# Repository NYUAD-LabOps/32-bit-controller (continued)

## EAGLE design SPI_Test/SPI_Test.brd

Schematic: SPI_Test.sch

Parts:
C1, C2, C3, C4, C5, C7, C8, C9, C14, C15, C19, C20, C23, C28, C29, C31, C43, C44, C45, C47, C48, C49, C50, C51, C52, C53, C54, C61, C62, C63, C64, C65, C66, C67, C68, C69, C91, C92, C93, C94, C95, C96, C97, C98, C99, C121, C122, C123, C124, C125, C126, C127, C128, C129, C151, C152, C153, C154, C155, C156, C157, C158, C159, C181, C182, C183, C184, C185, C186, C187, C188, C189: 0.1uF; 0402
C6, C46, C55, C70, C100, C130, C160, C190: 1uF; 0402
C10, C11, C39, C40, C57, C58, C87, C88, C117, C118, C147, C148, C177, C178: 12pF; 0402
C12, C13: 18pF; 0402
C21, C26, C56, C71, C101, C131, C161, C191: 10uF; 0402
C41, C42, C59, C60, C89, C90, C119, C120, C149, C150, C179, C180: 10pF; 0402
J1, J4, J6, J10, J15, J19, J23: 10-pos; 2X5
J3, J5, J9, J14, J18, J22: CONN_05X2PTH; 2X5
J13: 4-pos; 1X4_3.81MM_PITCH
L2: 2.2uH; 1008
LED2: Green; 0805
R1, R2, R3, R5, R6, R8, R10, R13, R15: 10K0; 0402
R4: 2K2; 0402
R12: 470R0; 0402
U1, U3, U6, U8, U10, U12: RENESAS_R7FS5D37A3A01CFM#AA0PLQP0064KB-C_REN-M; PLQP0064KB-C_REN-M
U2: S7G2LQFP176; LQFP176_24X24
X2, X3, X5, X7, X9, X11, X13: 32.768KHz; SMD_X_2_PADS
X4: 24MHz; SMD_3225
Y1, Y3, Y5, Y7, Y9, Y11: XTAL_12MHZ_ABM8G-12.000MHZ-B4Y-T; CRYSTAL_ABM8G_ABR

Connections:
DFI_01_A1: U1.50 (50/P501), U3.50 (50/P501), U6.50 (50/P501), U8.50 (50/P501), U10.50 (50/P501), U12.50 (50/P501)
DFI_02_A1: U1.62 (62/P002), U3.62 (62/P002), U6.62 (62/P002), U8.62 (62/P002), U10.62 (62/P002), U12.62 (62/P002)
DFO_01_A1: U1.30 (30/P302), U3.30 (30/P302), U6.30 (30/P302), U8.30 (30/P302), U10.30 (30/P302), U12.30 (30/P302)
DFO_02_A1: U1.41 (41/P107), U3.41 (41/P107), U6.41 (41/P107), U8.41 (41/P107), U10.41 (41/P107), U12.41 (41/P107)
DFO_03_A1: U1.42 (42/P106), U3.42 (42/P106), U6.42 (42/P106), U8.42 (42/P106), U10.42 (42/P106), U12.42 (42/P106)
DIR_M0A1: U1.15 (15/P408), U3.15 (15/P408), U6.15 (15/P408), U8.15 (15/P408), U10.15 (15/P408), U12.15 (15/P408)
DIR_M1A1: U1.3 (3/P402), U3.3 (3/P402), U6.3 (3/P402), U8.3 (3/P402), U10.3 (3/P402), U12.3 (3/P402)
ENABLE_M0A1: U1.14 (14/P409), U3.14 (14/P409), U6.14 (14/P409), U8.14 (14/P409), U10.14 (14/P409), U12.14 (14/P409)
ENABLE_M1A1: U1.2 (2/P401), U3.2 (2/P401), U6.2 (2/P401), U8.2 (2/P401), U10.2 (2/P401), U12.2 (2/P401)
ESTOP: U2.69 (P2_0(INPUT_ONLY))
ESTOP_A1: U1.27 (27/P200), U3.27 (27/P200), U6.27 (27/P200), U8.27 (27/P200), U10.27 (27/P200), U12.27 (27/P200)
GND: C1.P$1 (1), C2.P$1 (1), C3.P$1 (1), C4.P$1 (1), C5.P$2 (2), C6.P$2 (2), C7.P$1 (1), C8.P$1 (1), C9.P$2 (2), C10.P$2 (2), C11.P$2 (2), C12.P$2 (2), C13.P$2 (2), C14.P$1 (1), C15.P$1 (1), C19.P$2 (2), C20.P$2 (2), C21.P$2 (2), C23.P$1 (1), C26.P$2 (2), C28.P$2 (2), C29.P$2 (2), C31.P$2 (2), C39.P$2 (2), C40.P$2 (2), C41.P$2 (2), C42.P$2 (2), C43.P$2 (2), C44.P$1 (1), C45.P$1 (1), C46.P$1 (1), C47.P$2 (2), C48.P$2 (2), C49.P$2 (2), C50.P$1 (1), C51.P$1 (1), C52.P$2 (2), C53.P$2 (2), C54.P$2 (2), C55.P$2 (2), C56.P$2 (2), C57.P$2 (2), C58.P$2 (2), C59.P$2 (2), C60.P$2 (2), C61.P$2 (2), C62.P$2 (2), C63.P$2 (2), C64.P$2 (2), C65.P$1 (1), C66.P$1 (1), C67.P$2 (2), C68.P$2 (2), C69.P$2 (2), C70.P$2 (2), C71.P$2 (2), C87.P$2 (2), C88.P$2 (2), C89.P$2 (2), C90.P$2 (2), C91.P$2 (2), C92.P$2 (2), C93.P$2 (2), C94.P$2 (2), C95.P$1 (1), C96.P$1 (1), C97.P$2 (2), C98.P$2 (2), C99.P$2 (2), C100.P$2 (2), C101.P$2 (2), C117.P$2 (2), C118.P$2 (2), C119.P$2 (2), C120.P$2 (2), C121.P$2 (2), C122.P$2 (2), C123.P$2 (2), C124.P$2 (2), C125.P$1 (1), C126.P$1 (1), C127.P$2 (2), C128.P$2 (2), C129.P$2 (2), C130.P$2 (2), C131.P$2 (2), C147.P$2 (2), C148.P$2 (2), C149.P$2 (2), C150.P$2 (2), C151.P$2 (2), C152.P$2 (2), C153.P$2 (2), C154.P$2 (2), C155.P$1 (1), C156.P$1 (1), C157.P$2 (2), C158.P$2 (2), C159.P$2 (2), C160.P$2 (2), C161.P$2 (2), C177.P$2 (2), C178.P$2 (2), C179.P$2 (2), C180.P$2 (2), C181.P$2 (2), C182.P$2 (2), C183.P$2 (2), C184.P$2 (2), C185.P$1 (1), C186.P$1 (1), C187.P$2 (2), C188.P$2 (2), C189.P$2 (2), C190.P$2 (2), C191.P$2 (2), J1.6, J1.8, J1.10, J3.1, J3.2, J4.6, J4.8, J4.10, J5.1, J5.2, J6.6, J6.8, J6.10, J9.1, J9.2, J10.6, J10.8, J10.10, J13.P$1, J13.P$3, J13.P$4, J14.1, J14.2, J15.6, J15.8, J15.10, J18.1, J18.2, J19.6, J19.8, J19.10, J22.1, J22.2, J23.6, J23.8, J23.10, LED2.2 (C), R1.P$1 (1), R2.P$1 (1), R4.P$1 (1), U1.8 (8/VSS), U1.17 (17/VSS_USB), U1.28 (28/VSS), U1.39 (39/VSS), U1.55 (55/VREFL), U1.58 (58/AVSS0), U1.59 (59/VREFL0), U2.22 (VSS1), U2.28 (AVSS_USBHS), U2.29 (PVSS_USBHS), U2.30 (VSS2_USBHS), U2.33 (VSS1_USBHS), U2.35 (VSSIO), U2.45 (VSS_USB), U2.60 (VSS(IO)2), U2.63 (VSS(IO/DCDC)), U2.66 (VCC_DCDC(IO/DCDC)), U2.83 (VSS(IO)3), U2.98 (VSS(IO)4), U2.111 (VSS(IO)5), U2.124 (VSS(IO)6), U2.139 (VSS(IO)7), U2.150 (VSS(IO)8), U2.153 (VREFL), U2.156 (AVSS0), U2.157 (VREFL0), U2.170 (VSS(IO)9), U3.8 (8/VSS), U3.17 (17/VSS_USB), U3.28 (28/VSS), U3.39 (39/VSS), U3.55 (55/VREFL), U3.58 (58/AVSS0), U3.59 (59/VREFL0), U6.8 (8/VSS), U6.17 (17/VSS_USB), U6.28 (28/VSS), U6.39 (39/VSS), U6.55 (55/VREFL), U6.58 (58/AVSS0), U6.59 (59/VREFL0), U8.8 (8/VSS), U8.17 (17/VSS_USB), U8.28 (28/VSS), U8.39 (39/VSS), U8.55 (55/VREFL), U8.58 (58/AVSS0), U8.59 (59/VREFL0), U10.8 (8/VSS), U10.17 (17/VSS_USB), U10.28 (28/VSS), U10.39 (39/VSS), U10.55 (55/VREFL), U10.58 (58/AVSS0), U10.59 (59/VREFL0), U12.8 (8/VSS), U12.17 (17/VSS_USB), U12.28 (28/VSS), U12.39 (39/VSS), U12.55 (55/VREFL), U12.58 (58/AVSS0), U12.59 (59/VREFL0), X4.2, X4.4, Y1.2, Y1.4, Y3.2, Y3.4, Y5.2, Y5.4, Y7.2, Y7.4, Y9.2, Y9.4, Y11.2, Y11.4
HLFB_M0A1: U1.13 (13/P410), U3.13 (13/P410), U6.13 (13/P410), U8.13 (13/P410), U10.13 (13/P410), U12.13 (13/P410)
HLFB_M1A1: U1.1 (1/P400), U3.1 (1/P400), U6.1 (1/P400), U8.1 (1/P400), U10.1 (1/P400), U12.1 (1/P400)
LS_01_A1: U1.23 (23/P205), U3.23 (23/P205), U6.23 (23/P205), U8.23 (23/P205), U10.23 (23/P205), U12.23 (23/P205)
LS_02_A1: U1.53 (53/P015), U3.53 (53/P015), U6.53 (53/P015), U8.53 (53/P015), U10.53 (53/P015), U12.53 (53/P015)
LS_03_A1: U1.64 (64/P000), U3.64 (64/P000), U6.64 (64/P000), U8.64 (64/P000), U10.64 (64/P000), U12.64 (64/P000)
LS_04_A1: U1.63 (63/P001), U3.63 (63/P001), U6.63 (63/P001), U8.63 (63/P001), U10.63 (63/P001), U12.63 (63/P001)
LS_05: U2.81 (P3_5)
LS_06: U2.82 (P3_4)
MISO: J3.9, J3.10, J5.9, J5.10, J9.9, J9.10, J14.9, J14.10, J18.9, J18.10, J22.9, J22.10, U1.48 (48/P100), U2.132 (P1_0), U3.48 (48/P100), U6.48 (48/P100), U8.48 (48/P100), U10.48 (48/P100), U12.48 (48/P100)
MOSI: J3.7, J3.8, J5.7, J5.8, J9.7, J9.8, J14.7, J14.8, J18.7, J18.8, J22.7, J22.8, U1.47 (47/P101), U2.131 (P1_1), U3.47 (47/P101), U6.47 (47/P101), U8.47 (47/P101), U10.47 (47/P101), U12.47 (47/P101)
unnamed: C8.P$2 (2), U2.148 (VCL2)
unnamed: C9.P$1 (1), U2.19 (VCLO)
unnamed: LED2.1 (A), R12.P$1 (1)
unnamed: C5.P$1 (1), U2.62 (VCL1)
unnamed: R2.P$2 (2), U2.64 (VLO1(DCDC))
unnamed: R1.P$2 (2), U2.65 (VLO2(DCDC))
unnamed: R4.P$2 (2), U2.27 (USBHS_RREF)
unnamed: U1.18 (18/USB_DM), U3.18 (18/USB_DM), U6.18 (18/USB_DM), U8.18 (18/USB_DM), U10.18 (18/USB_DM), U12.18 (18/USB_DM)
unnamed: U1.19 (19/USB_DP), U3.19 (19/USB_DP), U6.19 (19/USB_DP), U8.19 (19/USB_DP), U10.19 (19/USB_DP), U12.19 (19/USB_DP)
unnamed: U1.26 (26/P201/MD), U3.26 (26/P201/MD), U6.26 (26/P201/MD), U8.26 (26/P201/MD), U10.26 (26/P201/MD), U12.26 (26/P201/MD)
unnamed: U1.36 (36/P111), U3.36 (36/P111), U6.36 (36/P111), U8.36 (36/P111), U10.36 (36/P111), U12.36 (36/P111)
unnamed: U1.37 (37/P112), U3.37 (37/P112), U6.37 (37/P112), U8.37 (37/P112), U10.37 (37/P112), U12.37 (37/P112)
unnamed: U1.40 (40/VCL), U3.40 (40/VCL), U6.40 (40/VCL), U8.40 (40/VCL), U10.40 (40/VCL), U12.40 (40/VCL)
unnamed: U1.43 (43/P105), U3.43 (43/P105), U6.43 (43/P105), U8.43 (43/P105), U10.43 (43/P105), U12.43 (43/P105)
unnamed: U1.44 (44/P104), U3.44 (44/P104), U6.44 (44/P104), U8.44 (44/P104), U10.44 (44/P104), U12.44 (44/P104)
P0_00: U2.169 (P0_0/AN0\00)
P0_01: U2.168 (P0_1/AN001)
P0_02: U2.167 (P0_2/AN002)
P0_03: U2.166 (P0_3/PGAVSS000)
P0_04: U2.165 (P0_4/AN100)
P0_05: U2.164 (P0_5/AN101)
P0_06: U2.163 (P0_6/AN102)
P0_07: U2.162 (P0_7/PGVSS100)
P0_08: U2.161 (P0_8/AN003)
P0_09: U2.160 (P0_9/AN004)
P0_10: U2.159 (P0_10/AN103)
P0_14: U2.152 (P0_14/DA0/AN005/AN105)
P0_15: U2.151 (P0_15/DA1/AN006/AN106)
P1_11: U2.92 (P1_11)
P1_12: U2.93 (P1_12)
P1_13: U2.94 (P1_13)
P1_14: U2.95 (P1_14)
P1_15: U2.96 (P1_15)
P2_01: U2.68 (P2_1/MD)
P2_02: U2.54 (P2_2)
P2_03: U2.53 (P2_3)
P2_04: U2.52 (P2_4)
P2_05: U2.51 (P2_5)
P2_06: U2.50 (P2_6)
P2_07: U2.49 (P2_7)
P3_01: U2.87 (P3_1)
P3_02: U2.86 (P3_2)
P3_03: U2.85 (P3_3)
P3_06: U2.80 (P3_6)
P3_07: U2.79 (P3_7)
P3_08: U2.78 (P3_8)
P3_09: U2.77 (P3_9)
P3_10: U2.76 (P3_10)
P3_11: U2.75 (P3_11)
P3_12: U2.74 (P3_12)
P3_13: U2.55 (P3_13)
P3_14: U2.56 (P3_14)
P3_15: U2.57 (P3_15)
P4_00: U2.1 (P4_0)
P4_01: U2.2 (P4_1)
P4_02: U2.3 (P4_2)
P4_03: U2.4 (P4_3)
P4_04: U2.5 (P4_4)
P4_05: U2.6 (P4_5)
P4_06: U2.7 (P4_6)
P4_08: U2.43 (P4_8)
P4_09: U2.42 (P4_9)
P4_10: U2.41 (P4_10)
P4_11: U2.40 (P4_11)
P4_12: U2.39 (P4_12)
P4_13: U2.38 (P4_13)
P4_14: U2.37 (P4_14)
P4_15: U2.36 (P4_15)
P5_00: U2.140 (P5_0/AN016)
P5_01: U2.141 (P5_1/AN116)
P5_02: U2.142 (P5_2/AN017)
P5_03: U2.143 (P5_3/AN117)
P5_04: U2.144 (P5_4/AN018)
P5_05: U2.145 (P5_5/AN118)
P5_06: U2.146 (P5_6/AN019)
P5_07: U2.147 (P5_7/AN119)
P5_11: U2.176 (P5_11)
P5_12: U2.175 (P5_12)
P5_13: U2.174 (P5_13)
P6_01: U2.121 (P6_1)
P6_02: U2.120 (P6_2)
P6_03: U2.119 (P6_3)
P6_04: U2.118 (P6_4)
P6_05: U2.117 (P6_5)
P6_06: U2.116 (P6_6)
P6_07: U2.115 (P6_7)
P6_08: U2.99 (P6_8)
P6_09: U2.100 (P6_9)
P6_10: U2.101 (P6_10)
P6_11: U2.102 (P6_11)
P6_12: U2.103 (P6_12)
P6_13: U2.104 (P6_13)
P6_14: U2.105 (P6_14)
P6_15: U2.106 (P6_15)
P7_00: U2.8 (P7_0)
P7_01: U2.9 (P7_1)
P7_02: U2.10 (P7_2)
P7_03: U2.11 (P7_3)
P7_04: U2.12 (P7_4)
P7_05: U2.13 (P7_5)
P7_06: U2.14 (P7_6)
P7_07: U2.15 (P7_7)
P8_00: U2.133 (P8_0)
P8_01: U2.134 (P8_1)
P8_02: U2.135 (P8_2)
P8_03: U2.136 (P8_3)
P8_04: U2.137 (P8_4)
P8_05: U2.173 (P8_5)
P8_06: U2.172 (P8_6)
P9_00: U2.58 (P9_0)
P9_01: U2.59 (P9_1)
P9_05: U2.73 (P9_5)
P9_06: U2.72 (P9_6)
P9_07: U2.71 (P9_7)
P9_08: U2.70 (P9_8)
PA_00: U2.114 (PA_0)
PA_01: U2.113 (PA_1)
PA_08: U2.107 (PA_8)
PA_09: U2.108 (PA_9)
PA_10: U2.109 (PA_10)
PB_00: U2.16 (PB_0)
RELAY_1_A1: U1.24 (24/P204), U3.24 (24/P204), U6.24 (24/P204), U8.24 (24/P204), U10.24 (24/P204), U12.24 (24/P204)
RELAY_2_A1: U1.21 (21/P207), U3.21 (21/P207), U6.21 (21/P207), U8.21 (21/P207), U10.21 (21/P207), U12.21 (21/P207)
RELAY_3_A1: U1.22 (22/P206), U3.22 (22/P206), U6.22 (22/P206), U8.22 (22/P206), U10.22 (22/P206), U12.22 (22/P206)
RELAY_4_A1: U1.31 (31/P301), U3.31 (31/P301), U6.31 (31/P301), U8.31 (31/P301), U10.31 (31/P301), U12.31 (31/P301)
RESET: C26.P$1 (1), J1.9, R3.P$1 (1), U2.67 (RES#)
RESET_A1: C56.P$1 (1), C71.P$1 (1), C101.P$1 (1), C131.P$1 (1), C161.P$1 (1), C191.P$1 (1), J4.9, J6.9, J10.9, J15.9, J19.9, J23.9, R5.P$1 (1), R6.P$1 (1), R8.P$1 (1), R10.P$1 (1), R13.P$1 (1), R15.P$1 (1), U1.25 (25/RES), U3.25 (25/RES), U6.25 (25/RES), U8.25 (25/RES), U10.25 (25/RES), U12.25 (25/RES)
SCLK: J3.5, J3.6, J5.5, J5.6, J9.5, J9.6, J14.5, J14.6, J18.5, J18.6, J22.5, J22.6, U1.46 (46/P102), U2.130 (P1_2), U3.46 (46/P102), U6.46 (46/P102), U8.46 (46/P102), U10.46 (46/P102), U12.46 (46/P102)
SSL0_A1_01: J3.3, J3.4, U1.45 (45/P103), U2.129 (P1_3)
SSL0_A1_02: J5.3, J5.4, U2.128 (P1_4), U3.45 (45/P103)
SSL0_A1_03: J9.3, J9.4, U2.127 (P1_5), U6.45 (45/P103)
SSL0_A1_04: J14.3, J14.4, U2.126 (P1_6), U8.45 (45/P103)
SSL0_A1_05: J18.3, J18.4, U2.125 (P1_7), U10.45 (45/P103)
SSL0_A1_06: J22.3, J22.4, U2.122 (P6_0), U12.45 (45/P103)
STEP_M0A1: U1.16 (16/P407), U3.16 (16/P407), U6.16 (16/P407), U8.16 (16/P407), U10.16 (16/P407), U12.16 (16/P407)
STEP_M1A1: U1.12 (12/P411), U3.12 (12/P411), U6.12 (12/P411), U8.12 (12/P411), U10.12 (12/P411), U12.12 (12/P411)
TCK: J1.7, J4.7, J6.7, J10.7, J15.7, J19.7, J23.7, U1.32 (32/P300/TCK/SWCLK), U2.88 (P3_0), U3.32 (32/P300/TCK/SWCLK), U6.32 (32/P300/TCK/SWCLK), U8.32 (32/P300/TCK/SWCLK), U10.32 (32/P300/TCK/SWCLK), U12.32 (32/P300/TCK/SWCLK)
TDI: J1.1, J4.1, J6.1, J10.1, J15.1, J19.1, J23.1, U1.35 (35/P110/TDI), U2.91 (P1_10), U3.35 (35/P110/TDI), U6.35 (35/P110/TDI), U8.35 (35/P110/TDI), U10.35 (35/P110/TDI), U12.35 (35/P110/TDI)
TDO: J1.3, J4.3, J6.3, J10.3, J15.3, J19.3, J23.3, U1.34 (34/P109/TDO/SWO), U2.90 (P1_9), U3.34 (34/P109/TDO/SWO), U6.34 (34/P109/TDO/SWO), U8.34 (34/P109/TDO/SWO), U10.34 (34/P109/TDO/SWO), U12.34 (34/P109/TDO/SWO)
TMS: J1.5, J4.5, J6.5, J10.5, J15.5, J19.5, J23.5, U1.33 (33/P108/TMS/SWDIO), U2.89 (P1_8), U3.33 (33/P108/TMS/SWDIO), U6.33 (33/P108/TMS/SWDIO), U8.33 (33/P108/TMS/SWDIO), U10.33 (33/P108/TMS/SWDIO), U12.33 (33/P108/TMS/SWDIO)
USBHS_DN: U2.31 (USBHS_DM)
USBHS_DP: U2.32 (USBHS_DP)
USBHS_VBUS: U2.17 (PB_1)
USB_DN: U2.46 (USB_DM)
USB_DP: U2.47 (USB_DP)
USB_VBUS_B: U2.44 (P4_7)
VBATT_M1A1: U1.4 (4/VBATT), U3.4 (4/VBATT), U6.4 (4/VBATT), U8.4 (4/VBATT), U10.4 (4/VBATT), U12.4 (4/VBATT)
VCL0_A1: C50.P$2 (2), C65.P$2 (2), C95.P$2 (2), C125.P$2 (2), C155.P$2 (2), C185.P$2 (2), U1.5 (5/VCL0), U3.5 (5/VCL0), U6.5 (5/VCL0), U8.5 (5/VCL0), U10.5 (5/VCL0), U12.5 (5/VCL0)
VCL_F(FLASH): C7.P$2 (2), U2.112 (VCL_F(FLASH))
VDD: C1.P$2 (2), C2.P$2 (2), C3.P$2 (2), C4.P$2 (2), C6.P$1 (1), C14.P$2 (2), C15.P$2 (2), C19.P$1 (1), C20.P$1 (1), C21.P$1 (1), C23.P$2 (2), C28.P$1 (1), C29.P$1 (1), C31.P$1 (1), C43.P$1 (1), C44.P$2 (2), C45.P$2 (2), C46.P$2 (2), C47.P$1 (1), C48.P$1 (1), C49.P$1 (1), C51.P$2 (2), C52.P$1 (1), C53.P$1 (1), C54.P$1 (1), C55.P$1 (1), C61.P$1 (1), C62.P$1 (1), C63.P$1 (1), C64.P$1 (1), C66.P$2 (2), C67.P$1 (1), C68.P$1 (1), C69.P$1 (1), C70.P$1 (1), C91.P$1 (1), C92.P$1 (1), C93.P$1 (1), C94.P$1 (1), C96.P$2 (2), C97.P$1 (1), C98.P$1 (1), C99.P$1 (1), C100.P$1 (1), C121.P$1 (1), C122.P$1 (1), C123.P$1 (1), C124.P$1 (1), C126.P$2 (2), C127.P$1 (1), C128.P$1 (1), C129.P$1 (1), C130.P$1 (1), C151.P$1 (1), C152.P$1 (1), C153.P$1 (1), C154.P$1 (1), C156.P$2 (2), C157.P$1 (1), C158.P$1 (1), C159.P$1 (1), C160.P$1 (1), C181.P$1 (1), C182.P$1 (1), C183.P$1 (1), C184.P$1 (1), C186.P$2 (2), C187.P$1 (1), C188.P$1 (1), C189.P$1 (1), C190.P$1 (1), J1.2, J1.4, J4.2, J4.4, J6.2, J6.4, J10.2, J10.4, J15.2, J15.4, J19.2, J19.4, J23.2, J23.4, L2.2, R3.P$2 (2), R5.P$2 (2), R6.P$2 (2), R8.P$2 (2), R10.P$2 (2), R12.P$2 (2), R13.P$2 (2), R15.P$2 (2), U1.11 (11/VCC), U1.20 (20/VCC_USB), U1.29 (29/VCC), U1.38 (38/VCC), U1.51 (51/VCC), U1.56 (56/VREFH), U1.57 (57/AVCC0), U1.60 (60/VREFH0), U2.25 (VCC1), U2.26 (AVCC_SUBHS), U2.34 (VCC_USBHS), U2.48 (VCC_USB), U2.61 (VCC(IO)2), U2.84 (VCC(IO)3), U2.97 (VCC(IO)4), U2.110 (VCC(IO)5), U2.123 (VCC(IO)6), U2.138 (VCC(IO)7), U2.149 (VCC(IO)8), U2.154 (VREFH), U2.155 (AVCC0), U2.158 (VREFH0), U2.171 (VCC(IO)9), U3.11 (11/VCC), U3.20 (20/VCC_USB), U3.29 (29/VCC), U3.38 (38/VCC), U3.51 (51/VCC), U3.56 (56/VREFH), U3.57 (57/AVCC0), U3.60 (60/VREFH0), U6.11 (11/VCC), U6.20 (20/VCC_USB), U6.29 (29/VCC), U6.38 (38/VCC), U6.51 (51/VCC), U6.56 (56/VREFH), U6.57 (57/AVCC0), U6.60 (60/VREFH0), U8.11 (11/VCC), U8.20 (20/VCC_USB), U8.29 (29/VCC), U8.38 (38/VCC), U8.51 (51/VCC), U8.56 (56/VREFH), U8.57 (57/AVCC0), U8.60 (60/VREFH0), U10.11 (11/VCC), U10.20 (20/VCC_USB), U10.29 (29/VCC), U10.38 (38/VCC), U10.51 (51/VCC), U10.56 (56/VREFH), U10.57 (57/AVCC0), U10.60 (60/VREFH0), U12.11 (11/VCC), U12.20 (20/VCC_USB), U12.29 (29/VCC), U12.38 (38/VCC), U12.51 (51/VCC), U12.56 (56/VREFH), U12.57 (57/AVCC0), U12.60 (60/VREFH0)
VDDIN: J13.P$2, L2.1
XCIN: C10.P$1 (1), U2.20 (XCIN), X3.P$1
XCIN_A1: C39.P$1 (1), C57.P$1 (1), C87.P$1 (1), C117.P$1 (1), C147.P$1 (1), C177.P$1 (1), U1.6 (6/XCIN), U3.6 (6/XCIN), U6.6 (6/XCIN), U8.6 (6/XCIN), U10.6 (6/XCIN), U12.6 (6/XCIN), X2.P$1, X5.P$1, X7.P$1, X9.P$1, X11.P$1, X13.P$1
XCOUT: C11.P$1 (1), U2.21 (XCOUT), X3.P$2
XCOUT_A1: C40.P$1 (1), C58.P$1 (1), C88.P$1 (1), C118.P$1 (1), C148.P$1 (1), C178.P$1 (1), U1.7 (7/XCOUT), U3.7 (7/XCOUT), U6.7 (7/XCOUT), U8.7 (7/XCOUT), U10.7 (7/XCOUT), U12.7 (7/XCOUT), X2.P$2, X5.P$2, X7.P$2, X9.P$2, X11.P$2, X13.P$2
XTAL1: C12.P$1 (1), U2.23 (P2_13/XTAL), X4.1
XTAL1_A1: C41.P$1 (1), C59.P$1 (1), C89.P$1 (1), C119.P$1 (1), C149.P$1 (1), C179.P$1 (1), U1.9 (9/XTAL), U3.9 (9/XTAL), U6.9 (9/XTAL), U8.9 (9/XTAL), U10.9 (9/XTAL), U12.9 (9/XTAL), Y1.3, Y3.3, Y5.3, Y7.3, Y9.3, Y11.3
XTAL2: C13.P$1 (1), U2.24 (P2_12/EXTAL), X4.3
XTAL2_A1: C42.P$1 (1), C60.P$1 (1), C90.P$1 (1), C120.P$1 (1), C150.P$1 (1), C180.P$1 (1), U1.10 (10/EXTAL), U3.10 (10/EXTAL), U6.10 (10/EXTAL), U8.10 (10/EXTAL), U10.10 (10/EXTAL), U12.10 (10/EXTAL), Y1.1, Y3.1, Y5.1, Y7.1, Y9.1, Y11.1

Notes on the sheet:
JTAG
Power Input
SPI

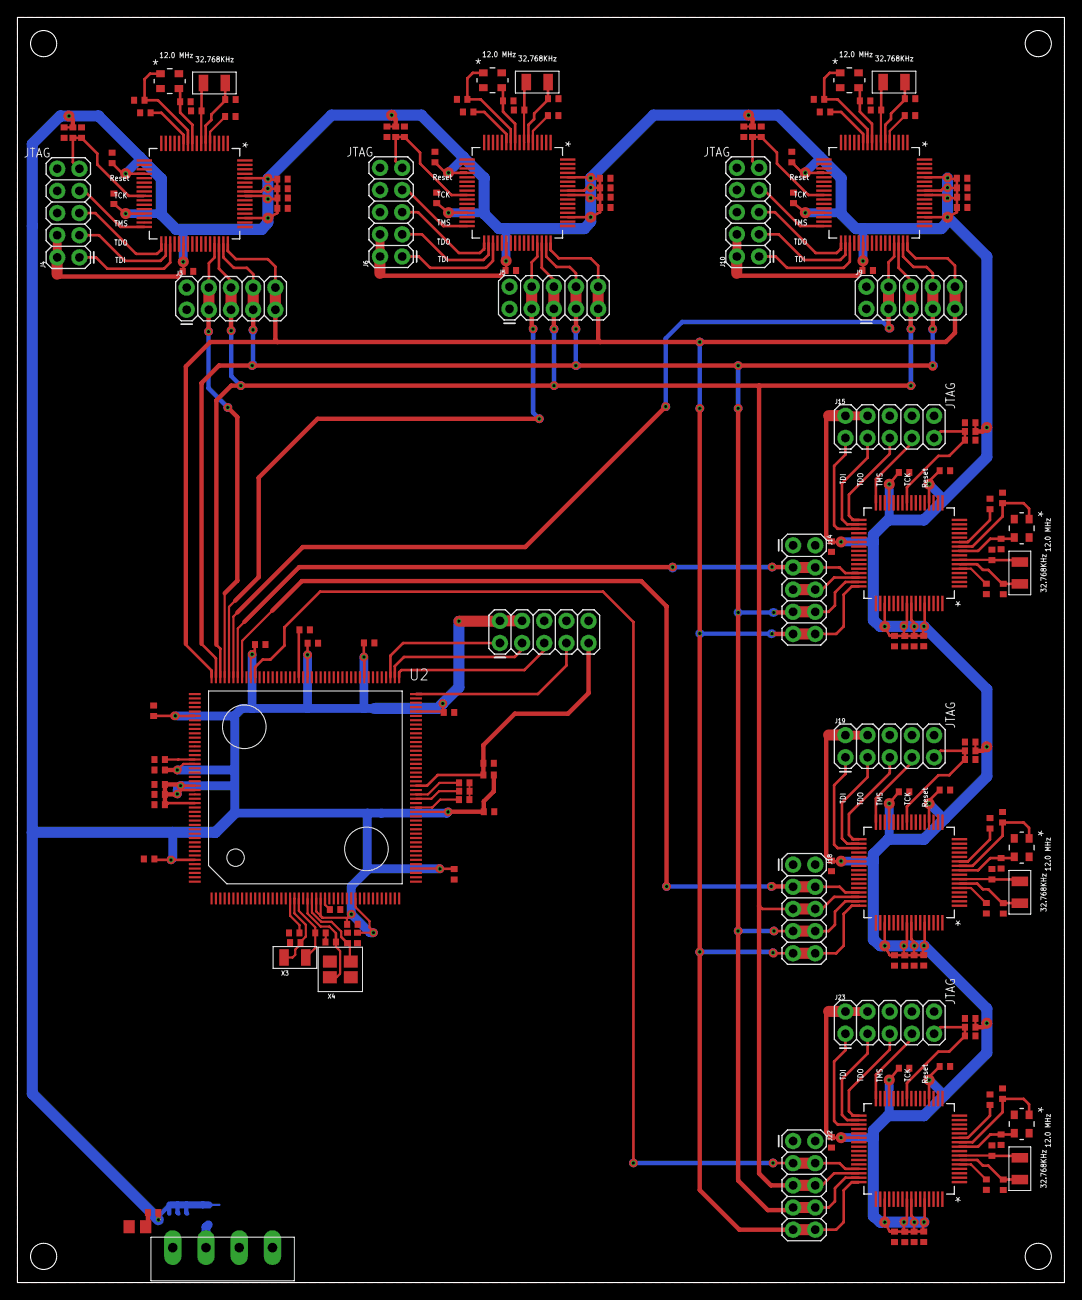
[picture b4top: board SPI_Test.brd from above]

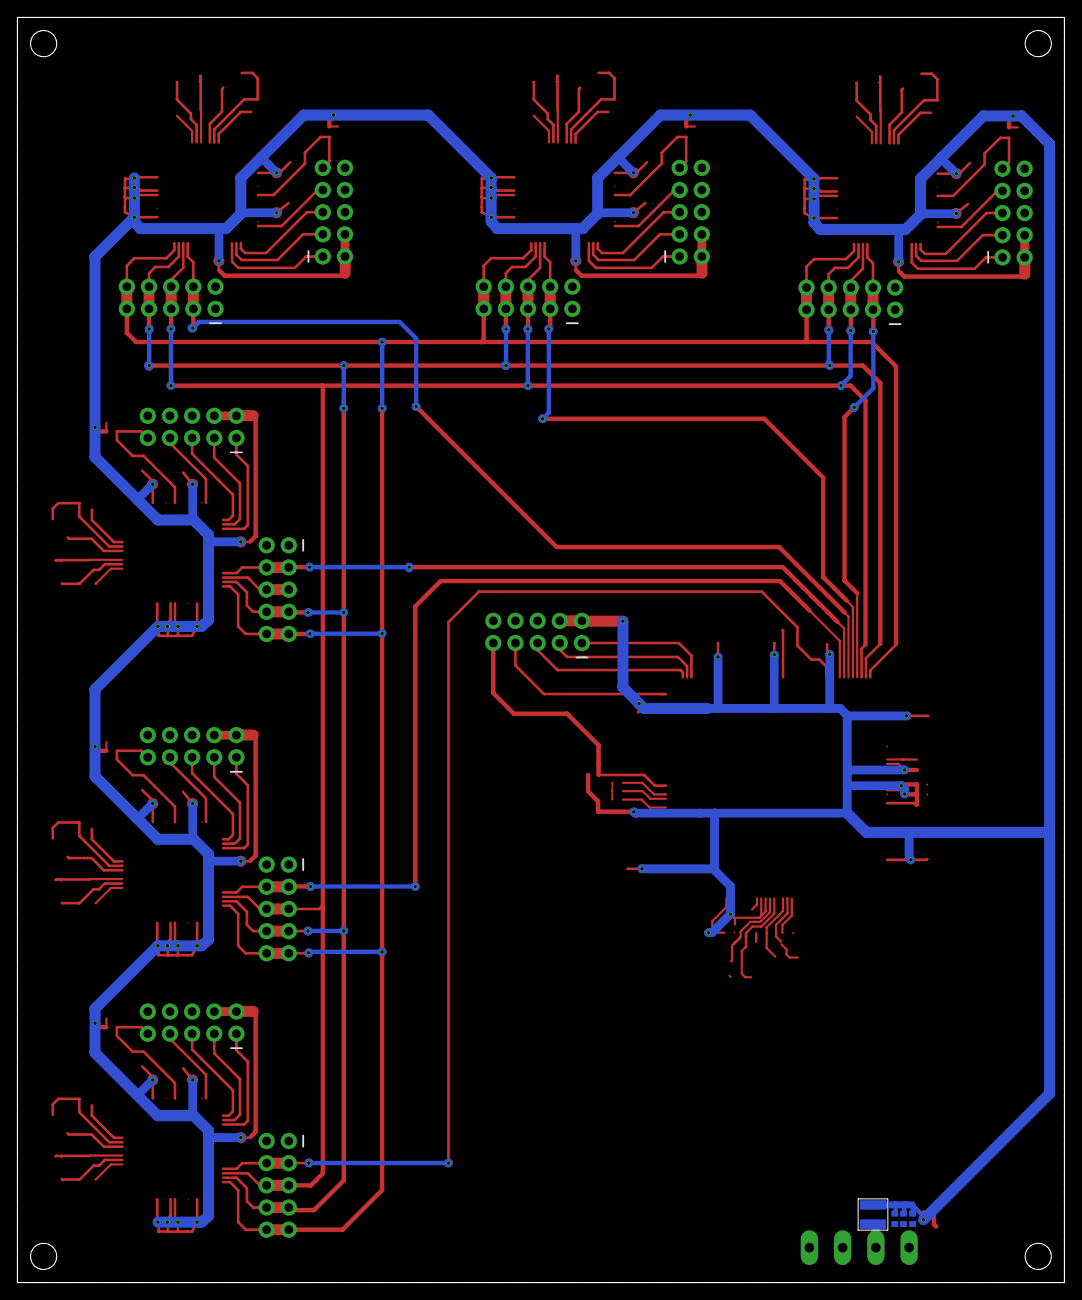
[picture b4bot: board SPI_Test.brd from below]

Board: 2 copper layers, 120.0 x 145.0 mm, 164 parts (4 on the bottom side), 66 nets.

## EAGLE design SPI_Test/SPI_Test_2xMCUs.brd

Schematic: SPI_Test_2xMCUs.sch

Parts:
C1, C2, C3, C4, C5, C7, C8, C9, C14, C15, C19, C20, C23, C28, C29, C31, C44, C45, C47, C48, C49, C50, C51, C52, C53, C54, C55, C58, C207, C208, C209, C210, C211, C212, C213, C214, C215, C218: 0.1uF; 0402
C6, C46, C56, C216: 1uF; 0402
C10, C11, C40, C41, C203, C204: 12pF; 0402
C12, C13: 18pF; 0402
C21, C26, C57, C217: 10uF; 0402
C42, C43, C205, C206: 10pF; 0402
J1, J4, J25: 10-pos; 2X5
J3, J24: CONN_05X2PTH; 2X5
J13: 4-pos; 1X4_3.81MM_PITCH
L2: 2.2uH; 1008
LED2: Green; 0805
R1, R2, R3, R5, R16: 10K0; 0402
R4: 2K2; 0402
R12: 470R0; 0402
U1, U13: RENESAS_R7FS5D37A3A01CFM#AA0PLQP0064KB-C_REN-M; PLQP0064KB-C_REN-M
U2: S7G2LQFP176; LQFP176_24X24
X2, X3, X14: 32.768KHz; SMD_X_2_PADS
X4: 24MHz; SMD_3225
Y1, Y12: XTAL_12MHZ_ABM8G-12.000MHZ-B4Y-T; CRYSTAL_ABM8G_ABR

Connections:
4/VBATT: U1.4 (4/VBATT), U13.4 (4/VBATT)
21/P207: U1.21 (21/P207), U13.21 (21/P207)
ESTOP: U2.69 (P2_0(INPUT_ONLY))
GND: C1.P$1 (1), C2.P$1 (1), C3.P$1 (1), C4.P$1 (1), C5.P$2 (2), C6.P$2 (2), C7.P$1 (1), C8.P$1 (1), C9.P$2 (2), C10.P$2 (2), C11.P$2 (2), C12.P$2 (2), C13.P$2 (2), C14.P$1 (1), C15.P$1 (1), C19.P$2 (2), C20.P$2 (2), C21.P$2 (2), C23.P$1 (1), C26.P$2 (2), C28.P$2 (2), C29.P$2 (2), C31.P$2 (2), C40.P$2 (2), C41.P$2 (2), C42.P$2 (2), C43.P$2 (2), C44.P$1 (1), C45.P$1 (1), C46.P$1 (1), C47.P$2 (2), C48.P$2 (2), C49.P$2 (2), C50.P$2 (2), C51.P$1 (1), C52.P$1 (1), C53.P$2 (2), C54.P$2 (2), C55.P$2 (2), C56.P$2 (2), C57.P$2 (2), C58.P$2 (2), C203.P$2 (2), C204.P$2 (2), C205.P$2 (2), C206.P$2 (2), C207.P$2 (2), C208.P$2 (2), C209.P$2 (2), C210.P$2 (2), C211.P$1 (1), C212.P$1 (1), C213.P$2 (2), C214.P$2 (2), C215.P$2 (2), C216.P$2 (2), C217.P$2 (2), C218.P$2 (2), J1.6, J1.8, J1.10, J3.1, J3.2, J4.6, J4.8, J4.10, J13.P$1, J13.P$3, J13.P$4, J24.1, J24.2, J25.6, J25.8, J25.10, LED2.2 (C), R1.P$1 (1), R2.P$1 (1), R4.P$1 (1), U1.8 (8/VSS), U1.17 (17/VSS_USB), U1.28 (28/VSS), U1.39 (39/VSS), U1.55 (55/VREFL), U1.58 (58/AVSS0), U1.59 (59/VREFL0), U2.22 (VSS1), U2.28 (AVSS_USBHS), U2.29 (PVSS_USBHS), U2.30 (VSS2_USBHS), U2.33 (VSS1_USBHS), U2.35 (VSSIO), U2.45 (VSS_USB), U2.60 (VSS(IO)2), U2.63 (VSS(IO/DCDC)), U2.66 (VCC_DCDC(IO/DCDC)), U2.83 (VSS(IO)3), U2.98 (VSS(IO)4), U2.111 (VSS(IO)5), U2.124 (VSS(IO)6), U2.139 (VSS(IO)7), U2.150 (VSS(IO)8), U2.153 (VREFL), U2.156 (AVSS0), U2.157 (VREFL0), U2.170 (VSS(IO)9), U13.8 (8/VSS), U13.17 (17/VSS_USB), U13.28 (28/VSS), U13.39 (39/VSS), U13.55 (55/VREFL), U13.58 (58/AVSS0), U13.59 (59/VREFL0), X4.2, X4.4, Y1.2, Y1.4, Y12.2, Y12.4
LS_05: U2.81 (P3_5)
LS_06: U2.82 (P3_4)
MISO: J3.9, J3.10, J24.9, J24.10, U1.48 (48/P100), U2.132 (P1_0), U13.48 (48/P100)
MOSI: J3.7, J3.8, J24.7, J24.8, U1.47 (47/P101), U2.131 (P1_1), U13.47 (47/P101)
unnamed: C8.P$2 (2), U2.148 (VCL2)
unnamed: C9.P$1 (1), U2.19 (VCLO)
unnamed: LED2.1 (A), R12.P$1 (1)
unnamed: C58.P$1 (1), U1.40 (40/VCL)
unnamed: C5.P$1 (1), U2.62 (VCL1)
unnamed: R2.P$2 (2), U2.64 (VLO1(DCDC))
unnamed: R1.P$2 (2), U2.65 (VLO2(DCDC))
unnamed: R4.P$2 (2), U2.27 (USBHS_RREF)
unnamed: C218.P$1 (1), U13.40 (40/VCL)
unnamed: U1.18 (18/USB_DM), U13.18 (18/USB_DM)
unnamed: U1.19 (19/USB_DP), U13.19 (19/USB_DP)
unnamed: U1.36 (36/P111), U13.36 (36/P111)
unnamed: U1.37 (37/P112), U13.37 (37/P112)
P0_00: U2.169 (P0_0/AN0\00)
P0_01: U2.168 (P0_1/AN001)
P0_02: U2.167 (P0_2/AN002)
P0_03: U2.166 (P0_3/PGAVSS000)
P0_04: U2.165 (P0_4/AN100)
P0_05: U2.164 (P0_5/AN101)
P0_06: U2.163 (P0_6/AN102)
P0_07: U2.162 (P0_7/PGVSS100)
P0_08: U2.161 (P0_8/AN003)
P0_09: U2.160 (P0_9/AN004)
P0_10: U2.159 (P0_10/AN103)
P0_14: U2.152 (P0_14/DA0/AN005/AN105)
P0_15: U2.151 (P0_15/DA1/AN006/AN106)
P1_11: U2.92 (P1_11)
P1_12: U2.93 (P1_12)
P1_13: U2.94 (P1_13)
P1_14: U2.95 (P1_14)
P1_15: U2.96 (P1_15)
P2_01: U2.68 (P2_1/MD)
P2_02: U2.54 (P2_2)
P2_03: U2.53 (P2_3)
P2_04: U2.52 (P2_4)
P2_05: U2.51 (P2_5)
P2_06: U2.50 (P2_6)
P2_07: U2.49 (P2_7)
P3_01: U2.87 (P3_1)
P3_02: U2.86 (P3_2)
P3_03: U2.85 (P3_3)
P3_06: U2.80 (P3_6)
P3_07: U2.79 (P3_7)
P3_08: U2.78 (P3_8)
P3_09: U2.77 (P3_9)
P3_10: U2.76 (P3_10)
P3_11: U2.75 (P3_11)
P3_12: U2.74 (P3_12)
P3_13: U2.55 (P3_13)
P3_14: U2.56 (P3_14)
P3_15: U2.57 (P3_15)
P4_00: U2.1 (P4_0)
P4_01: U2.2 (P4_1)
P4_02: U2.3 (P4_2)
P4_03: U2.4 (P4_3)
P4_04: U2.5 (P4_4)
P4_05: U2.6 (P4_5)
P4_06: U2.7 (P4_6)
P4_08: U2.43 (P4_8)
P4_09: U2.42 (P4_9)
P4_10: U2.41 (P4_10)
P4_11: U2.40 (P4_11)
P4_12: U2.39 (P4_12)
P4_13: U2.38 (P4_13)
P4_14: U2.37 (P4_14)
P4_15: U2.36 (P4_15)
P5_00: U2.140 (P5_0/AN016)
P5_01: U2.141 (P5_1/AN116)
P5_02: U2.142 (P5_2/AN017)
P5_03: U2.143 (P5_3/AN117)
P5_04: U2.144 (P5_4/AN018)
P5_05: U2.145 (P5_5/AN118)
P5_06: U2.146 (P5_6/AN019)
P5_07: U2.147 (P5_7/AN119)
P5_11: U2.176 (P5_11)
P5_12: U2.175 (P5_12)
P5_13: U2.174 (P5_13)
P6_01: U2.121 (P6_1)
P6_02: U2.120 (P6_2)
P6_03: U2.119 (P6_3)
P6_04: U2.118 (P6_4)
P6_05: U2.117 (P6_5)
P6_06: U2.116 (P6_6)
P6_07: U2.115 (P6_7)
P6_08: U2.99 (P6_8)
P6_09: U2.100 (P6_9)
P6_10: U2.101 (P6_10)
P6_11: U2.102 (P6_11)
P6_12: U2.103 (P6_12)
P6_13: U2.104 (P6_13)
P6_14: U2.105 (P6_14)
P6_15: U2.106 (P6_15)
P7_00: U2.8 (P7_0)
P7_01: U2.9 (P7_1)
P7_02: U2.10 (P7_2)
P7_03: U2.11 (P7_3)
P7_04: U2.12 (P7_4)
P7_05: U2.13 (P7_5)
P7_06: U2.14 (P7_6)
P7_07: U2.15 (P7_7)
P8_00: U2.133 (P8_0)
P8_01: U2.134 (P8_1)
P8_02: U2.135 (P8_2)
P8_03: U2.136 (P8_3)
P8_04: U2.137 (P8_4)
P8_05: U2.173 (P8_5)
P8_06: U2.172 (P8_6)
P9_00: U2.58 (P9_0)
P9_01: U2.59 (P9_1)
P9_05: U2.73 (P9_5)
P9_06: U2.72 (P9_6)
P9_07: U2.71 (P9_7)
P9_08: U2.70 (P9_8)
PA_00: U2.114 (PA_0)
PA_01: U2.113 (PA_1)
PA_08: U2.107 (PA_8)
PA_09: U2.108 (PA_9)
PA_10: U2.109 (PA_10)
PB_00: U2.16 (PB_0)
RESET: C26.P$1 (1), J1.9, R3.P$1 (1), U2.67 (RES#)
RESET_A1: C57.P$1 (1), C217.P$1 (1), J4.9, J25.9, R5.P$1 (1), R16.P$1 (1), U1.25 (25/RES), U13.25 (25/RES)
SCLK: J3.5, J3.6, J24.5, J24.6, U1.46 (46/P102), U2.130 (P1_2), U13.46 (46/P102)
SSL0_A1_01: J3.3, J3.4, U1.45 (45/P103), U2.129 (P1_3)
SSL0_A1_02: U2.128 (P1_4)
SSL0_A1_03: U2.127 (P1_5)
SSL0_A1_04: U2.126 (P1_6)
SSL0_A1_05: U2.125 (P1_7)
SSL0_A1_06: J24.3, J24.4, U2.122 (P6_0), U13.45 (45/P103)
TCK: J1.7, J4.7, J25.7, U1.32 (32/P300/TCK/SWCLK), U2.88 (P3_0), U13.32 (32/P300/TCK/SWCLK)
TDI: J1.1, J4.1, J25.1, U1.35 (35/P110/TDI), U2.91 (P1_10), U13.35 (35/P110/TDI)
TDO: J1.3, J4.3, J25.3, U1.34 (34/P109/TDO/SWO), U2.90 (P1_9), U13.34 (34/P109/TDO/SWO)
TMS: J1.5, J4.5, J25.5, U1.33 (33/P108/TMS/SWDIO), U2.89 (P1_8), U13.33 (33/P108/TMS/SWDIO)
USBHS_DN: U2.31 (USBHS_DM)
USBHS_DP: U2.32 (USBHS_DP)
USBHS_VBUS: U2.17 (PB_1)
USB_DN: U2.46 (USB_DM)
USB_DP: U2.47 (USB_DP)
USB_VBUS_B: U2.44 (P4_7)
VCL0_A1: C51.P$2 (2), C211.P$2 (2), U1.5 (5/VCL0), U13.5 (5/VCL0)
VCL_F(FLASH): C7.P$2 (2), U2.112 (VCL_F(FLASH))
VDD: C1.P$2 (2), C2.P$2 (2), C3.P$2 (2), C4.P$2 (2), C6.P$1 (1), C14.P$2 (2), C15.P$2 (2), C19.P$1 (1), C20.P$1 (1), C21.P$1 (1), C23.P$2 (2), C28.P$1 (1), C29.P$1 (1), C31.P$1 (1), C44.P$2 (2), C45.P$2 (2), C46.P$2 (2), C47.P$1 (1), C48.P$1 (1), C49.P$1 (1), C50.P$1 (1), C52.P$2 (2), C53.P$1 (1), C54.P$1 (1), C55.P$1 (1), C56.P$1 (1), C207.P$1 (1), C208.P$1 (1), C209.P$1 (1), C210.P$1 (1), C212.P$2 (2), C213.P$1 (1), C214.P$1 (1), C215.P$1 (1), C216.P$1 (1), J1.2, J1.4, J4.2, J4.4, J25.2, J25.4, L2.2, R3.P$2 (2), R5.P$2 (2), R12.P$2 (2), R16.P$2 (2), U1.11 (11/VCC), U1.20 (20/VCC_USB), U1.29 (29/VCC), U1.38 (38/VCC), U1.51 (51/VCC), U1.56 (56/VREFH), U1.57 (57/AVCC0), U1.60 (60/VREFH0), U2.25 (VCC1), U2.26 (AVCC_SUBHS), U2.34 (VCC_USBHS), U2.48 (VCC_USB), U2.61 (VCC(IO)2), U2.84 (VCC(IO)3), U2.97 (VCC(IO)4), U2.110 (VCC(IO)5), U2.123 (VCC(IO)6), U2.138 (VCC(IO)7), U2.149 (VCC(IO)8), U2.154 (VREFH), U2.155 (AVCC0), U2.158 (VREFH0), U2.171 (VCC(IO)9), U13.11 (11/VCC), U13.20 (20/VCC_USB), U13.29 (29/VCC), U13.38 (38/VCC), U13.51 (51/VCC), U13.56 (56/VREFH), U13.57 (57/AVCC0), U13.60 (60/VREFH0)
VDDIN: J13.P$2, L2.1
XCIN: C10.P$1 (1), U2.20 (XCIN), X3.P$1
XCIN_A1: C40.P$1 (1), C203.P$1 (1), U1.6 (6/XCIN), U13.6 (6/XCIN), X2.P$1, X14.P$1
XCOUT: C11.P$1 (1), U2.21 (XCOUT), X3.P$2
XCOUT_A1: C41.P$1 (1), C204.P$1 (1), U1.7 (7/XCOUT), U13.7 (7/XCOUT), X2.P$2, X14.P$2
XTAL1: C12.P$1 (1), U2.23 (P2_13/XTAL), X4.1
XTAL1_A1: C42.P$1 (1), C205.P$1 (1), U1.9 (9/XTAL), U13.9 (9/XTAL), Y1.3, Y12.3
XTAL2: C13.P$1 (1), U2.24 (P2_12/EXTAL), X4.3
XTAL2_A1: C43.P$1 (1), C206.P$1 (1), U1.10 (10/EXTAL), U13.10 (10/EXTAL), Y1.1, Y12.1

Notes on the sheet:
JTAG
Power Input
SPI

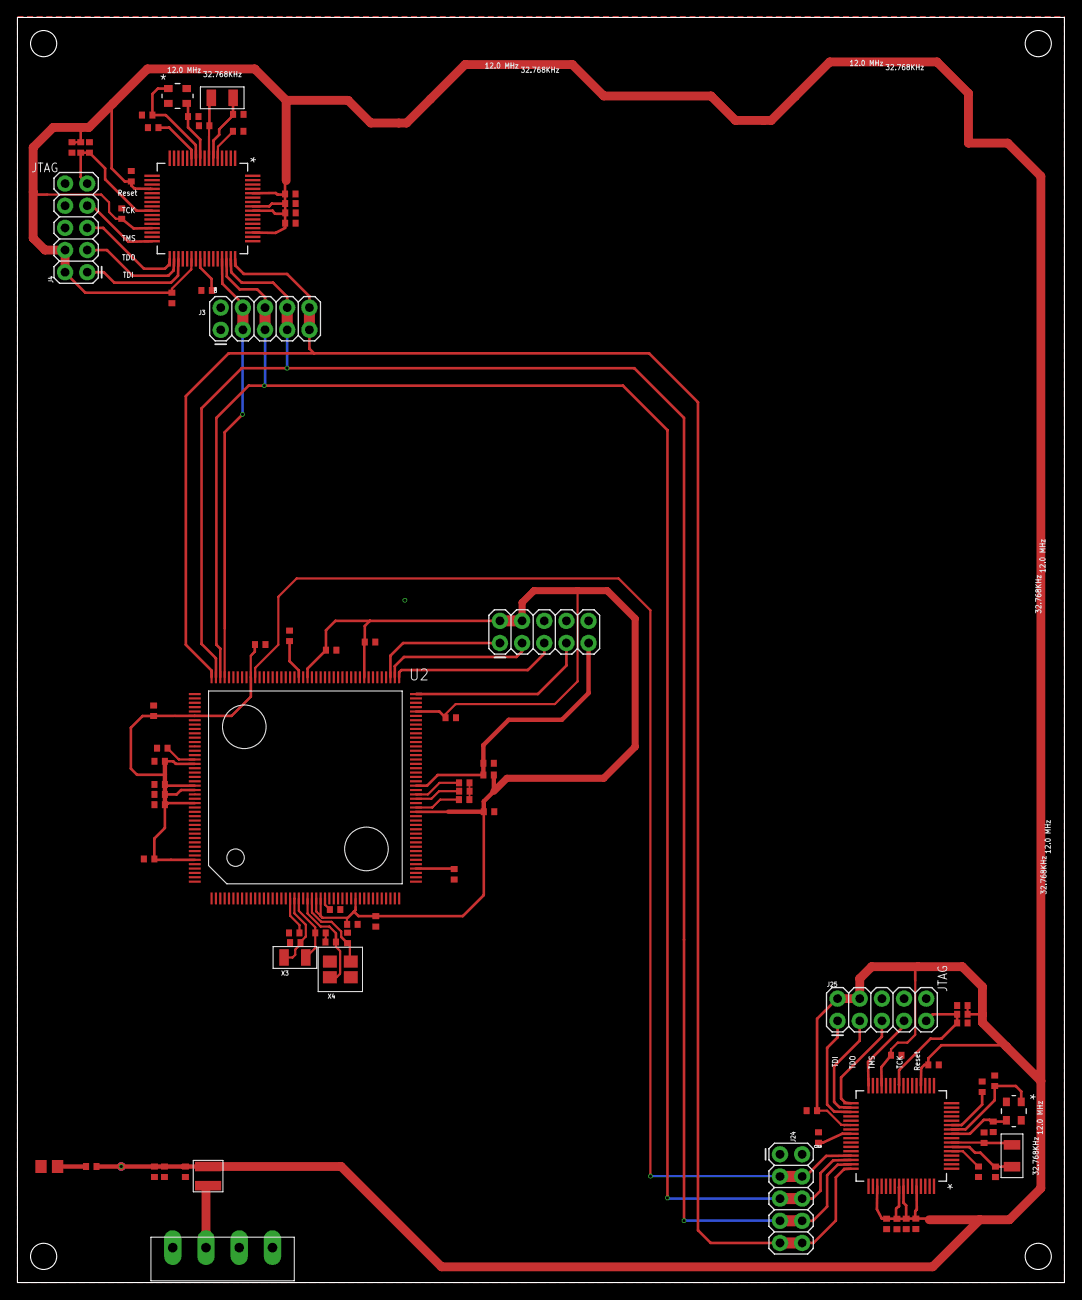
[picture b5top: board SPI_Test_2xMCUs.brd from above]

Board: 2 copper layers, 120.0 x 145.0 mm, 82 parts (0 on the bottom side), 39 nets.

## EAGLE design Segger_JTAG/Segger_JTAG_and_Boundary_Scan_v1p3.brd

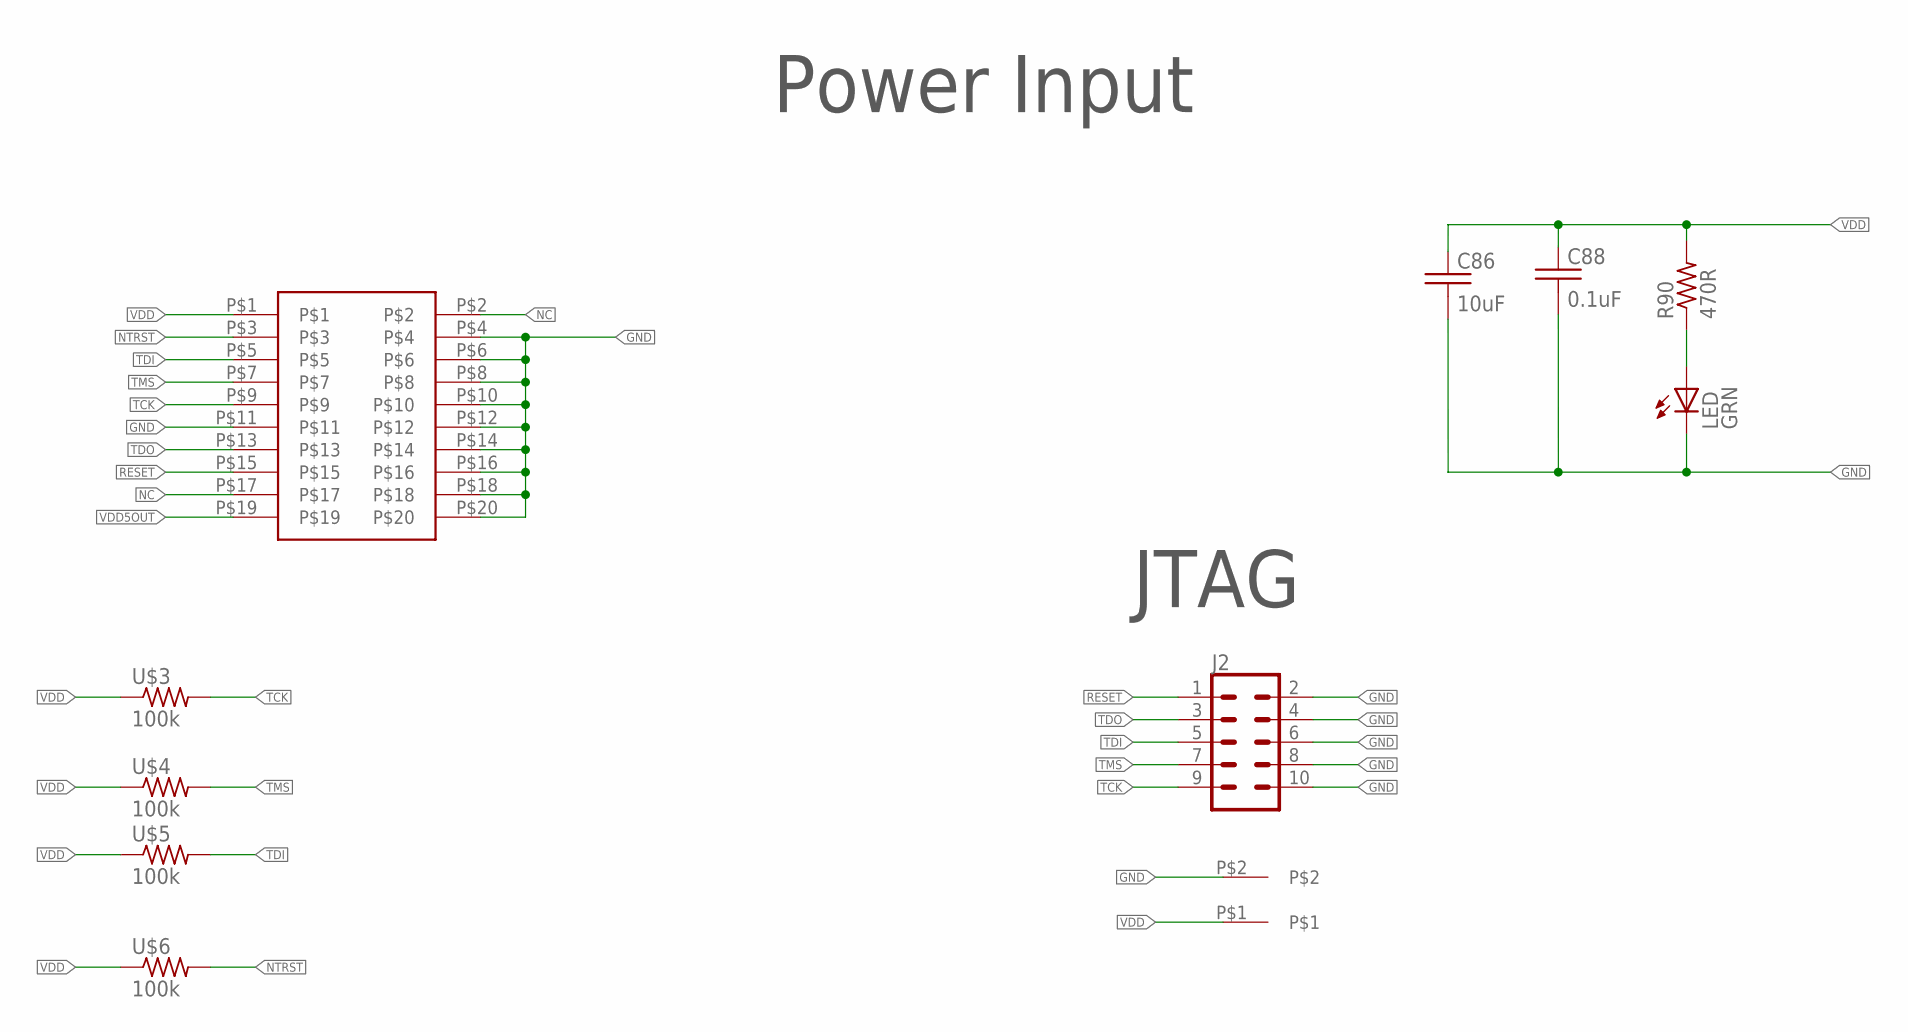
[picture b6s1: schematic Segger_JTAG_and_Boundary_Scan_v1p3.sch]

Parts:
C86: 10uF; 0805
C88: 0.1uF; 0805
J1: 2-pos; 2_3.81MM_PITCH
J2: CONN_05X2PTH; 2X5
LED: LED_0805_GREEN
R90: 470R; 0805
U$2: 2_X_10_HEADER_GENERIC; 2_X_10_.1_INCH
U$3, U$4, U$5, U$6: 100k; 0805

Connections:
GND: C86.2, C88.2, J1.P$2, J2.2, J2.4, J2.6, J2.8, J2.10, LED.C, U$2.P$4, U$2.P$6, U$2.P$8, U$2.P$10, U$2.P$11, U$2.P$12, U$2.P$14, U$2.P$16, U$2.P$18, U$2.P$20
unnamed: LED.A, R90.1
NC: U$2.P$2, U$2.P$17
NTRST: U$2.P$3, U$6.2
RESET: J2.1, U$2.P$15
TCK: J2.9, U$2.P$9, U$3.2
TDI: J2.5, U$2.P$5, U$5.2
TDO: J2.3, U$2.P$13
TMS: J2.7, U$2.P$7, U$4.2
VDD: C86.1, C88.1, J1.P$1, R90.2, U$2.P$1, U$3.1, U$4.1, U$5.1, U$6.1
VDD5OUT: U$2.P$19

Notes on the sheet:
Power Input
JTAG

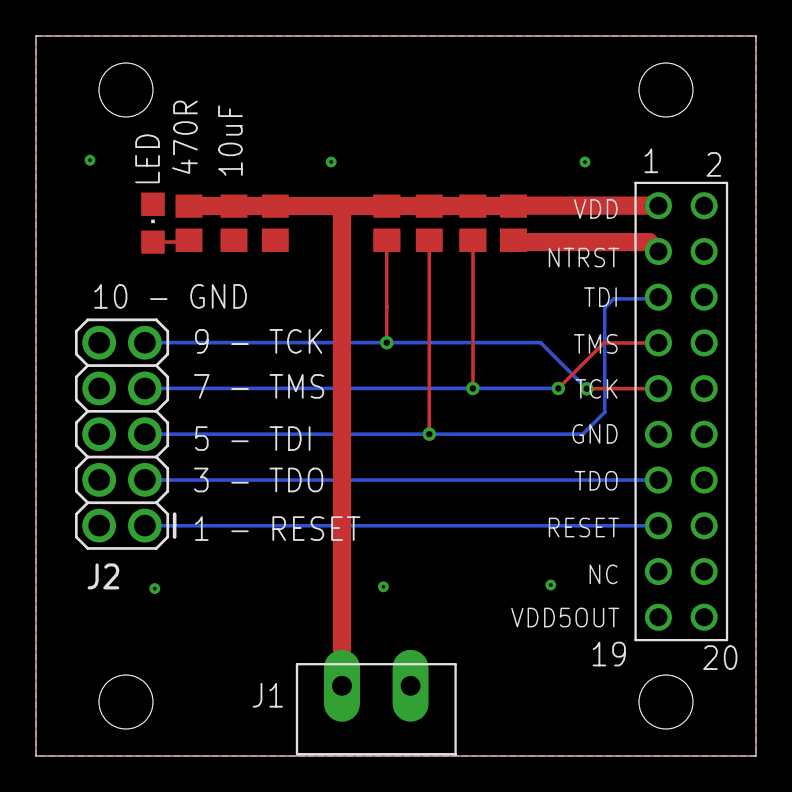
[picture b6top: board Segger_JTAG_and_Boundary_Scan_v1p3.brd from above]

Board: 2 copper layers, 40.0 x 40.0 mm, 11 parts (0 on the bottom side), 10 nets.
